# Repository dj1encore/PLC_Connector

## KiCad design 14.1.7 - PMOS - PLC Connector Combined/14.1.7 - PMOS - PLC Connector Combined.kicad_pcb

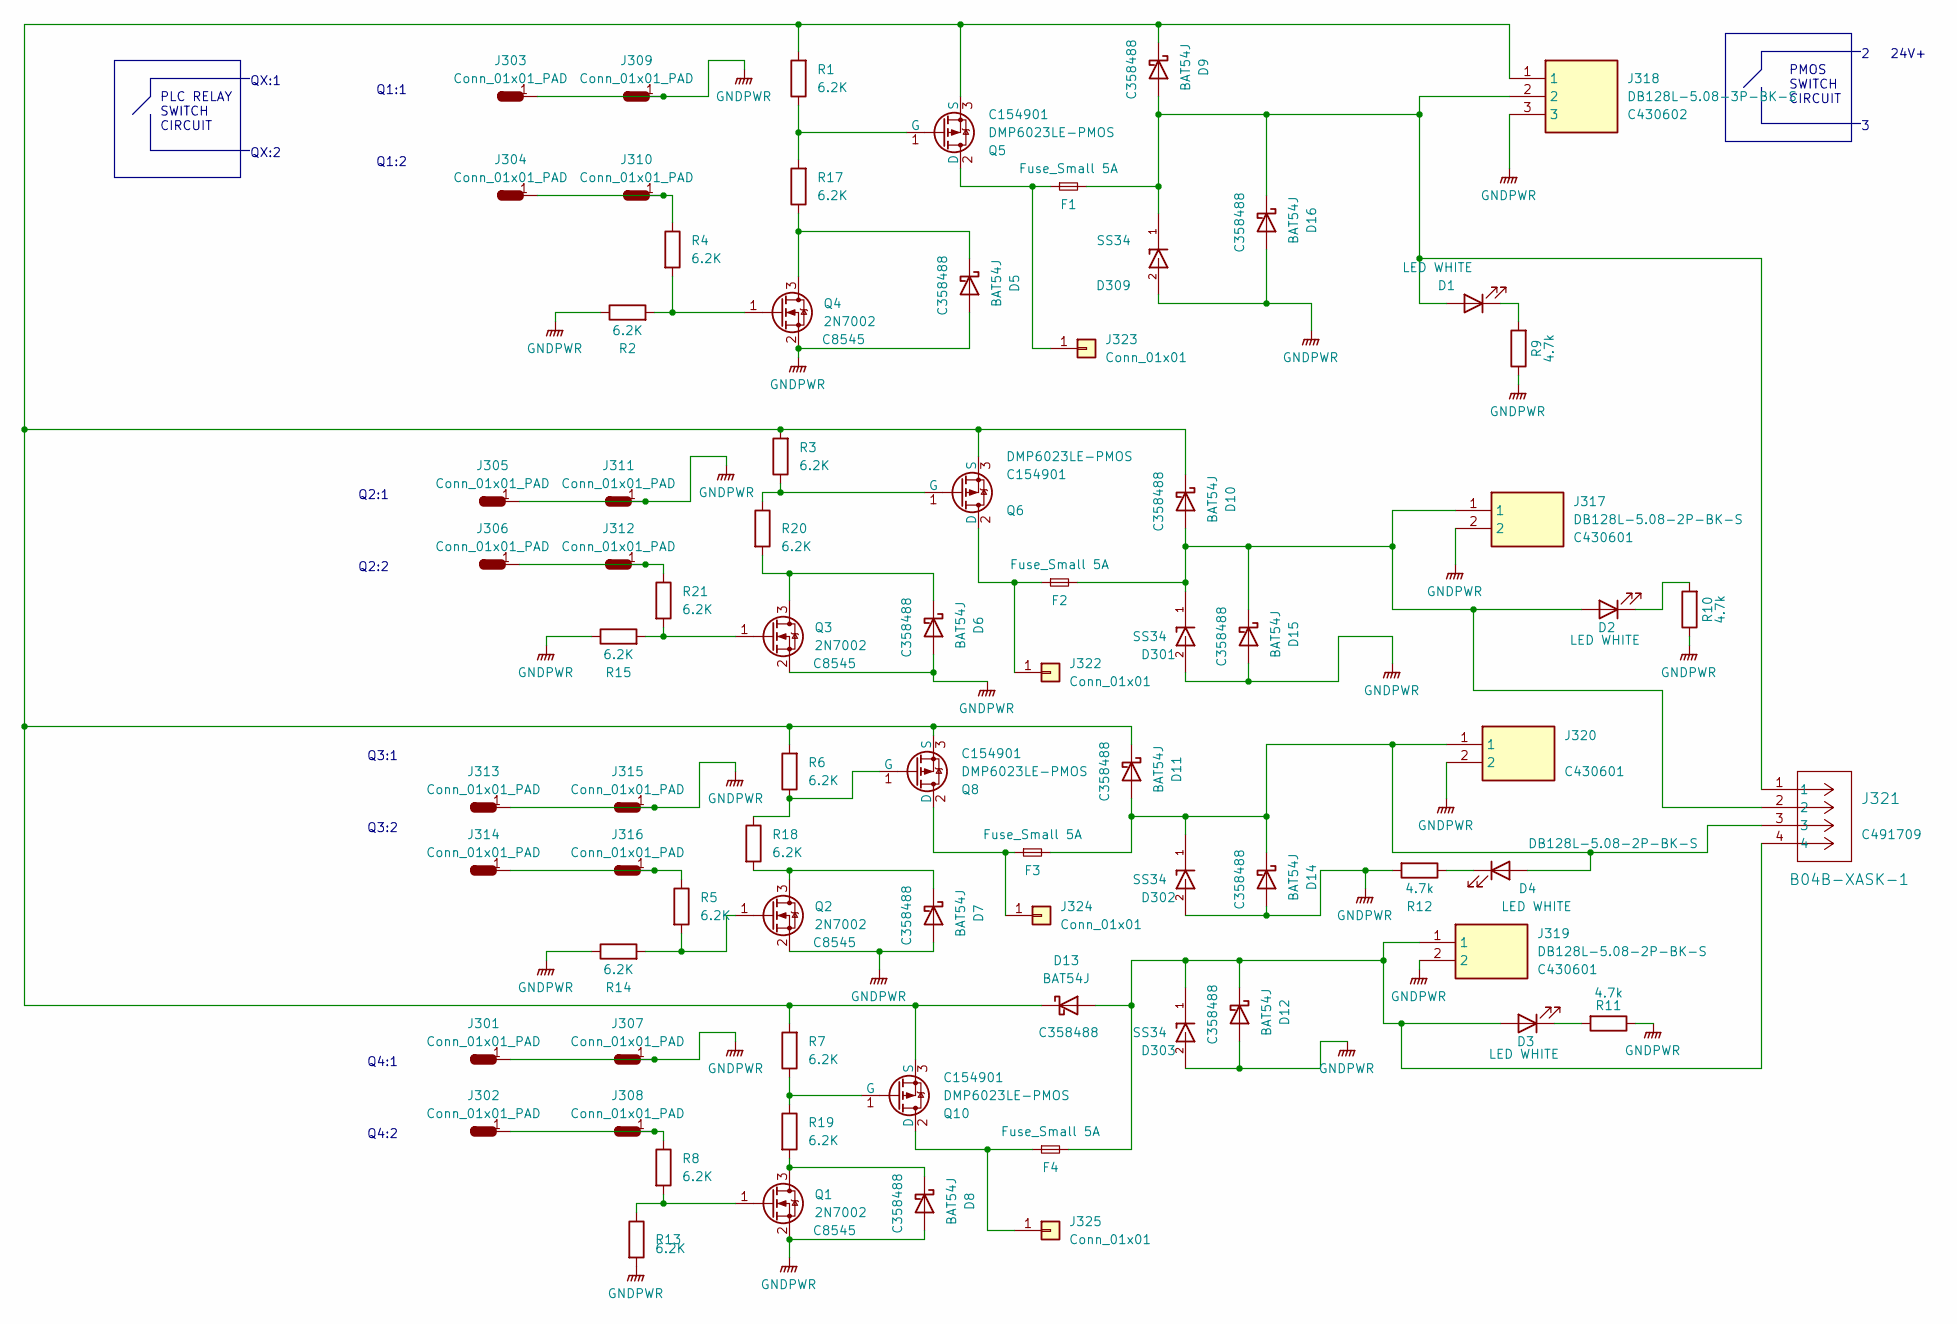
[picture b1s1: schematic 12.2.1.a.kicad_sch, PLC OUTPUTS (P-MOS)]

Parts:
D1, D2, D3, D4: LED WHITE; LED_0603_1608Metric; LCSC C2290
D5, D6, D7, D8, D9, D10, D11, D12, D13, D14, D15, D16: BAT54J; D_SOD-323F; LCSC C358488
D301, D302, D303, D309: SS34; D_SMA; LCSC C8678
F1, F2, F3, F4: Fuse_Small 5A; Fuse_1206_3216Metric_Pad1.42x1.75mm_HandSolder; LCSC C57525
J301, J302, J303, J304, J305, J306, J307, J308, J309, J310, J311, J312, J313, J314, J315, J316: Conn_01x01_PAD; Conn_pin_PLC
J317, J319, J320: DB128L-5.08-2P-BK-S; 1729128; Mouser Part Number 651-1729128
J318: DB128L-5.08-3P-BK-S; XY128V-A-5.08-3P; LCSC C430602
J321: B04B-XASK-1; CONN_B04B-XASK-1-A_JST; LCSC C491709
J322, J323, J324, J325: Conn_01x01; Pin_D0.7mm_L6.5mm_W1.8mm_FlatFork-MOD
Q1, Q2, Q3, Q4: 2N7002; SOT-23; LCSC C8545
Q5, Q6, Q8, Q10: DMP6023LE-PMOS; SOT-223 DMP6023LE; LCSC C154901
R1, R2, R3, R4, R5, R6, R7, R8, R13, R14, R15, R17, R18, R19, R20, R21: 6.2K; R_0603_1608Metric; LCSC C4260
R9, R10, R11, R12: 4.7k; R_0603_1608Metric; LCSC C88615

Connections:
GNDPWR: D5.2 (A), D6.2 (A), D7.2 (A), D8.2 (A), D12.2 (A), D14.2 (A), D15.2 (A), D16.2 (A), D301.2, D302.2, D303.2, D309.2, J301.1, J303.1, J305.1, J307.1, J309.1, J311.1, J313.1, J315.1, J317.2, J318.3, J319.2, J320.2, Q1.2 (S), Q2.2 (S), Q3.2 (S), Q4.2 (S), R2.1, R9.1, R10.1, R11.1, R12.2, R13.2, R14.1, R15.1
unnamed: D1.2 (A), D9.2 (A), D16.1 (K), D309.1, F1.2, J318.2, J321.1
unnamed: D1.1 (K), R9.2
unnamed: D2.1 (K), R10.2
unnamed: D3.1 (K), R11.2
unnamed: D4.1 (K), R12.1
unnamed: D5.1 (K), Q4.3 (D), R17.1
unnamed: D6.1 (K), Q3.3 (D), R20.2
unnamed: D7.1 (K), Q2.3 (D), R18.2
unnamed: D8.1 (K), Q1.3 (D), R19.2
unnamed: D2.2 (A), D10.2 (A), D15.1 (K), D301.1, F2.2, J317.1, J321.2
unnamed: D9.1 (K), D10.1 (K), D11.1 (K), D13.1 (K), J318.1, Q5.3 (S), Q6.3 (S), Q8.3 (S), Q10.3 (S), R1.2, R3.2, R6.2, R7.2
unnamed: D4.2 (A), D11.2 (A), D14.1 (K), D302.1, F3.2, J320.1, J321.3
unnamed: D3.2 (A), D12.1 (K), D13.2 (A), D303.1, F4.2, J319.1, J321.4
unnamed: J302.1, J308.1, R8.1
unnamed: J304.1, J310.1, R4.1
unnamed: J306.1, J312.1, R21.1
unnamed: J314.1, J316.1, R5.1
unnamed: F2.1, J322.1, Q6.2 (D)
unnamed: F1.1, J323.1, Q5.2 (D)
unnamed: F3.1, J324.1, Q8.2 (D)
unnamed: F4.1, J325.1, Q10.2 (D)
unnamed: Q1.1 (G), R8.2, R13.1
unnamed: Q2.1 (G), R5.2, R14.2
unnamed: Q3.1 (G), R15.2, R21.2
unnamed: Q4.1 (G), R2.2, R4.2
unnamed: Q5.1 (G), R1.1, R17.2
unnamed: Q6.1 (G), R3.1, R20.1
unnamed: Q8.1 (G), R6.1, R18.1
unnamed: Q10.1 (G), R7.1, R19.1

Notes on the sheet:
Q4:1
Q4:2
Q3:1
2 24V+
PMOS SWITCH CIRCUIT
QX:2
PLC RELAY SWITCH CIRCUIT
Q2:1
Q1:2
Q2:2
Q3:2
QX:1
Q1:1

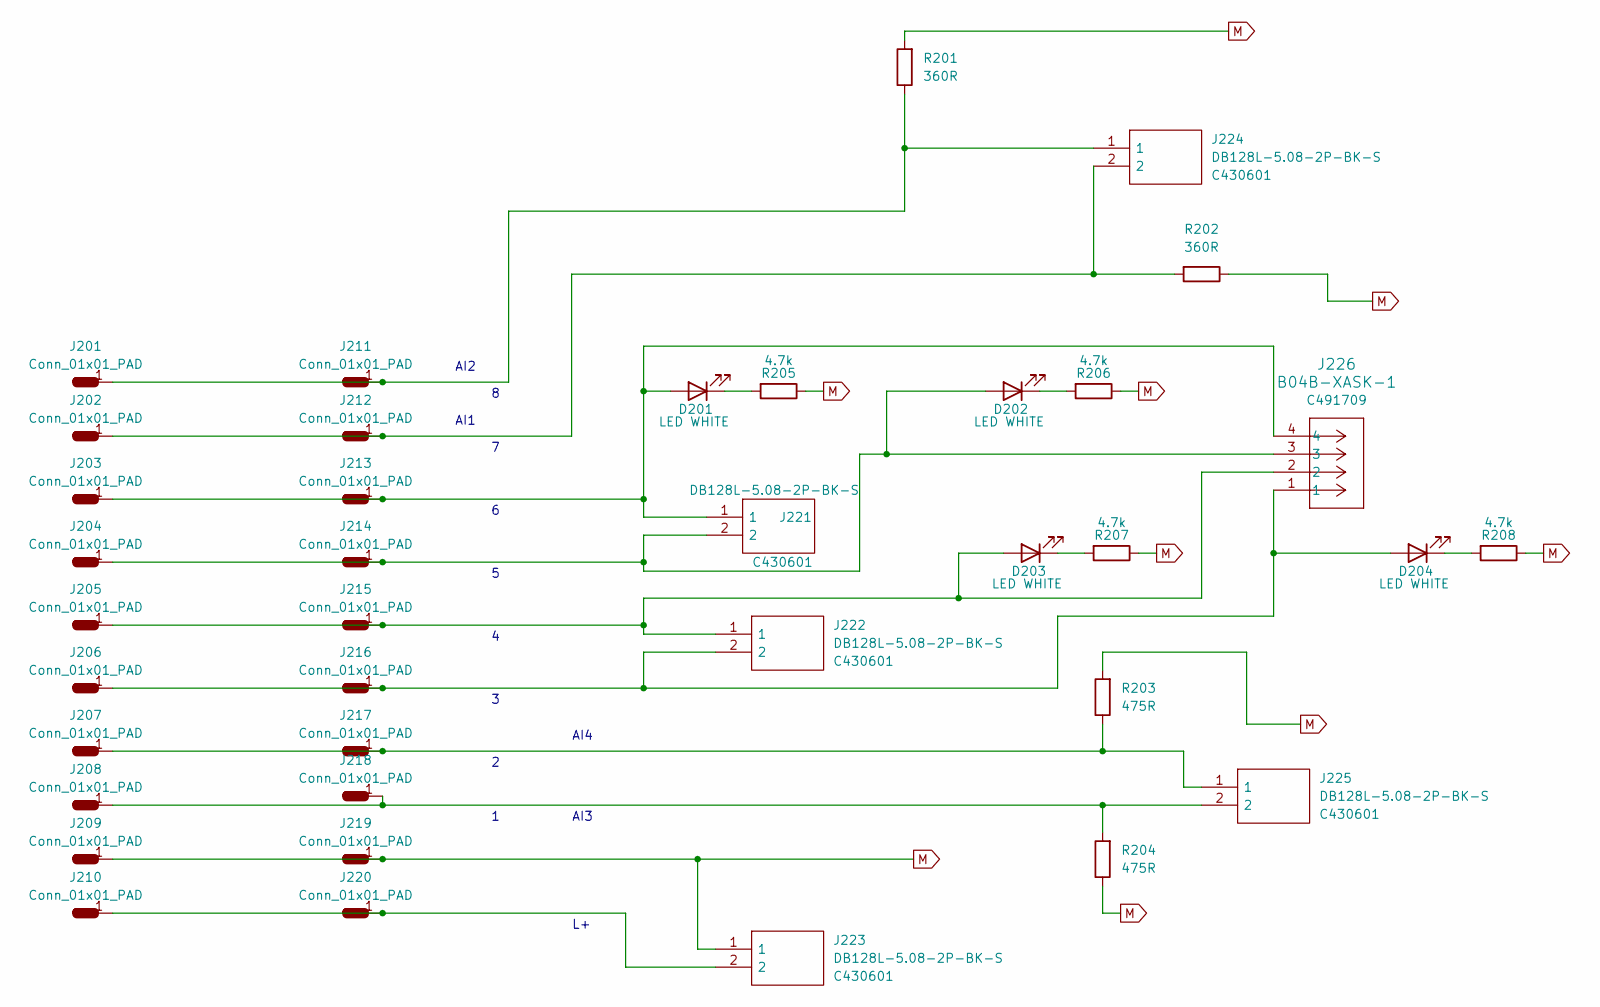
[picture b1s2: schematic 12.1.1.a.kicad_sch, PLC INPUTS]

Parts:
D201, D202, D203, D204: LED WHITE; LED_0603_1608Metric; LCSC C2290
J201, J202, J203, J204, J205, J206, J207, J208, J209, J210, J211, J212, J213, J214, J215, J216, J217, J218, J219, J220: Conn_01x01_PAD; Conn_pin_PLC
J221, J222, J223, J224, J225: DB128L-5.08-2P-BK-S; 1729128; Manufacturer_Part_Number 1729128; LCSC C430601
J226: B04B-XASK-1; CONN_B04B-XASK-1-A_JST; LCSC C491709
R201, R202: 360R; R_1206_3216Metric; LCSC C17932
R203, R204: 475R; R_1210_3225Metric; LCSC C784300
R205, R206, R207, R208: 4.7k; R_0603_1608Metric; LCSC C88615

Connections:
M: J209.1, J219.1, J223.1, R201.2, R202.1, R203.2, R204.1, R205.1, R206.1, R207.1, R208.1
unnamed: D201.2 (A), J203.1, J213.1, J221.1, J226.4
unnamed: D201.1 (K), R205.2
unnamed: D202.2 (A), J204.1, J214.1, J221.2, J226.3
unnamed: D202.1 (K), R206.2
unnamed: D203.2 (A), J205.1, J215.1, J222.1, J226.2
unnamed: D203.1 (K), R207.2
unnamed: D204.2 (A), J206.1, J216.1, J222.2, J226.1
unnamed: D204.1 (K), R208.2
unnamed: J201.1, J211.1, J224.1, R201.1
unnamed: J202.1, J212.1, J224.2, R202.2
unnamed: J207.1, J217.1, J225.1, R203.1
unnamed: J208.1, J218.1, J225.2, R204.2
unnamed: J210.1, J220.1, J223.2

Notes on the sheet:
AI2
AI3
AI4
AI1

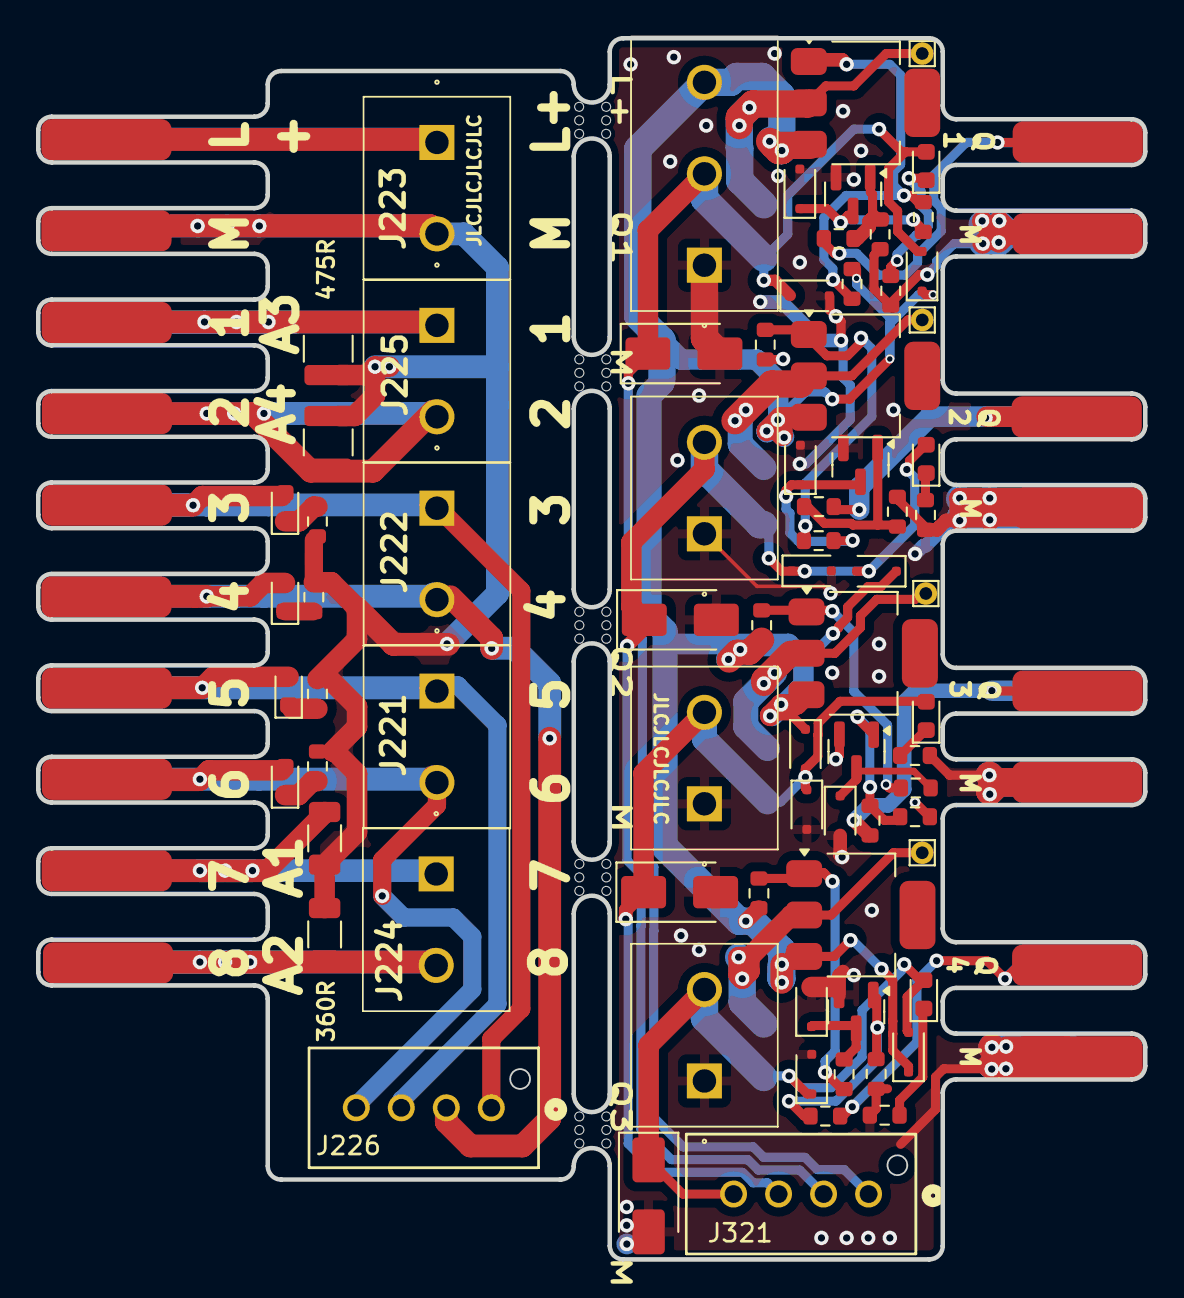
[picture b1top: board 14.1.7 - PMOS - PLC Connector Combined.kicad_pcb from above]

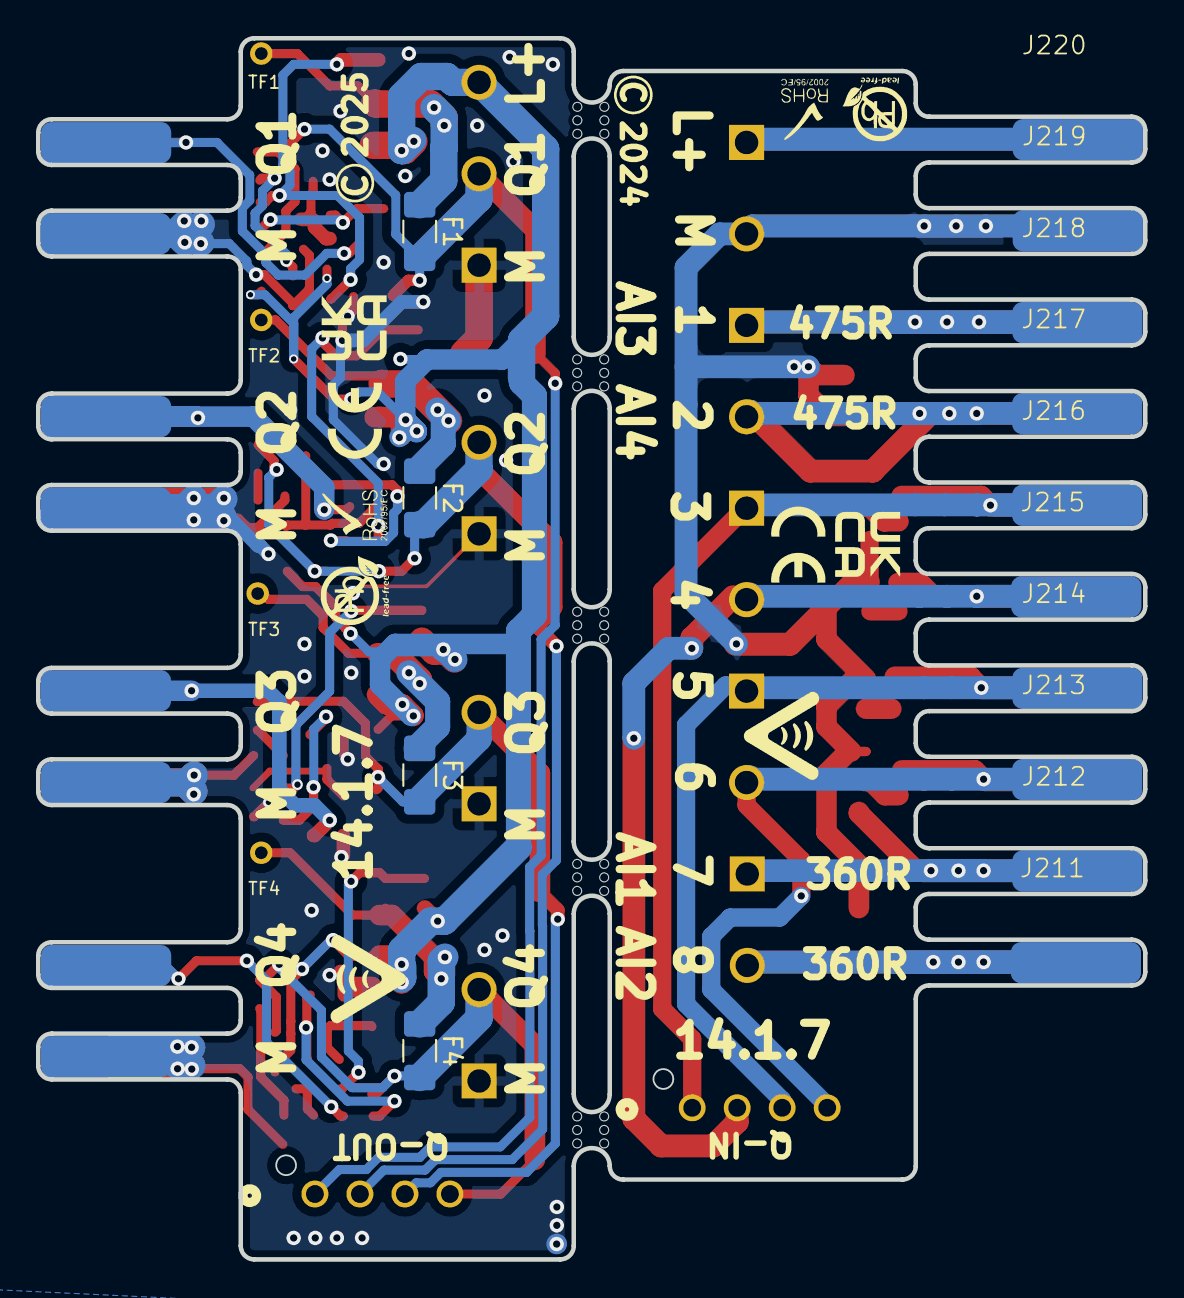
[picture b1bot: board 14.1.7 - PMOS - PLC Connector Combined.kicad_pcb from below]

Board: 2 copper layers, 61.5 x 67.8 mm, 120 parts (22 on the bottom side), 44 nets.

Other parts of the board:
mouse-bite-2mm-slot, mouse-bite-2mm-slot#2, mouse-bite-2mm-slot#3, mouse-bite-2mm-slot#4, mouse-bite-2mm-slot#5: VAL**; mouse-bite-2mm-slot

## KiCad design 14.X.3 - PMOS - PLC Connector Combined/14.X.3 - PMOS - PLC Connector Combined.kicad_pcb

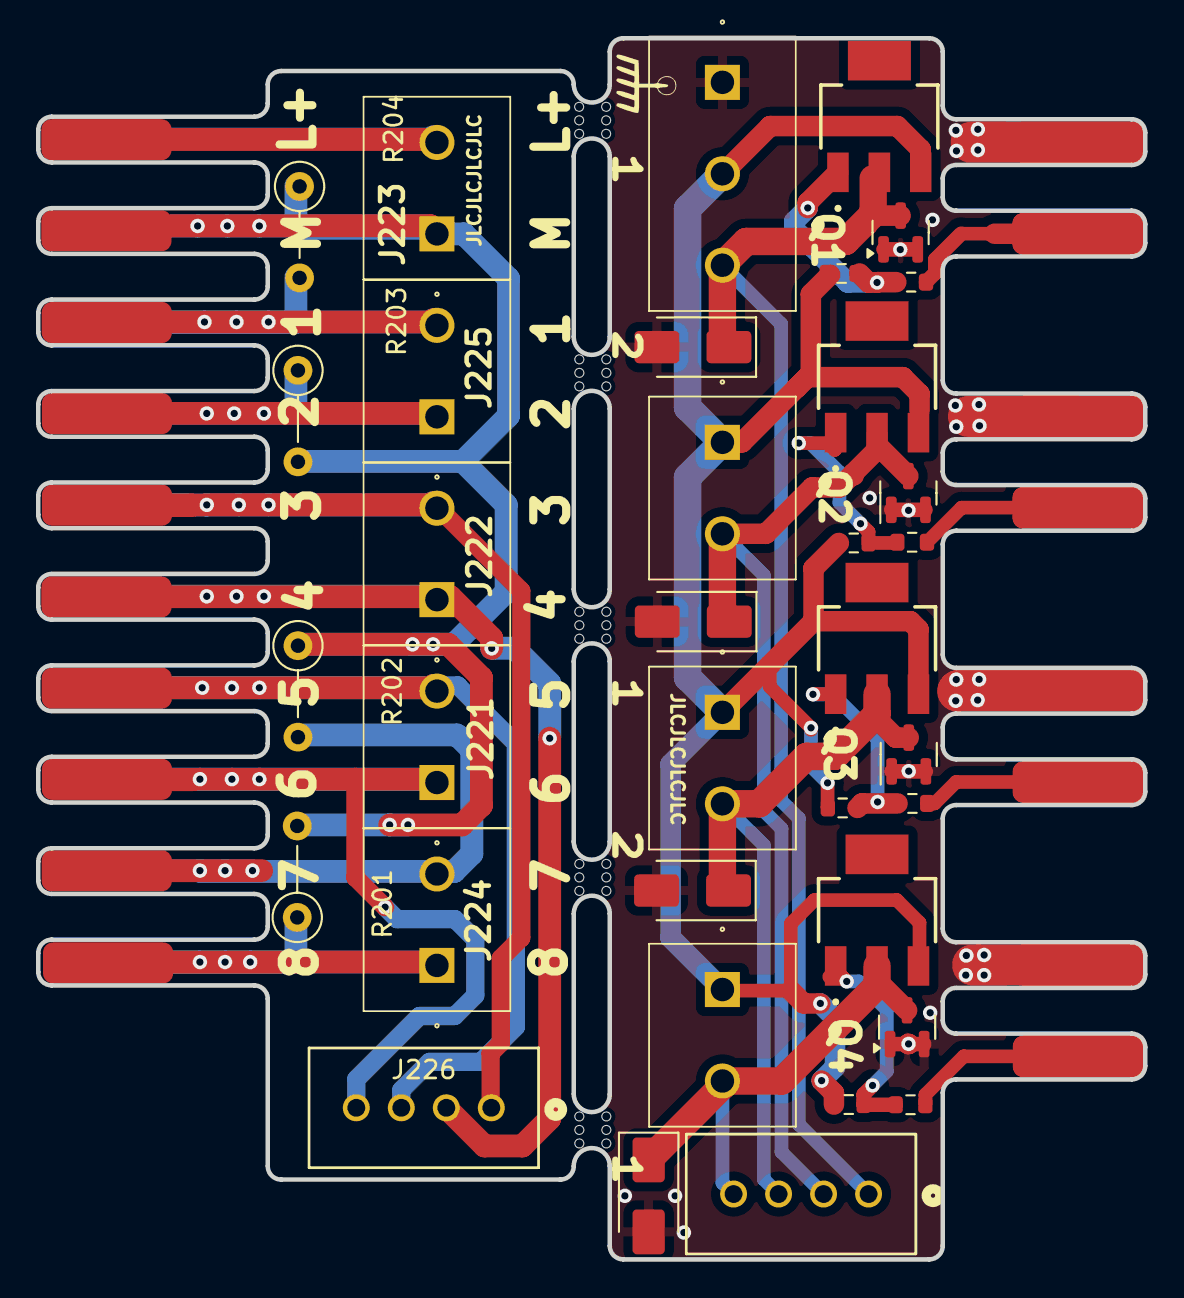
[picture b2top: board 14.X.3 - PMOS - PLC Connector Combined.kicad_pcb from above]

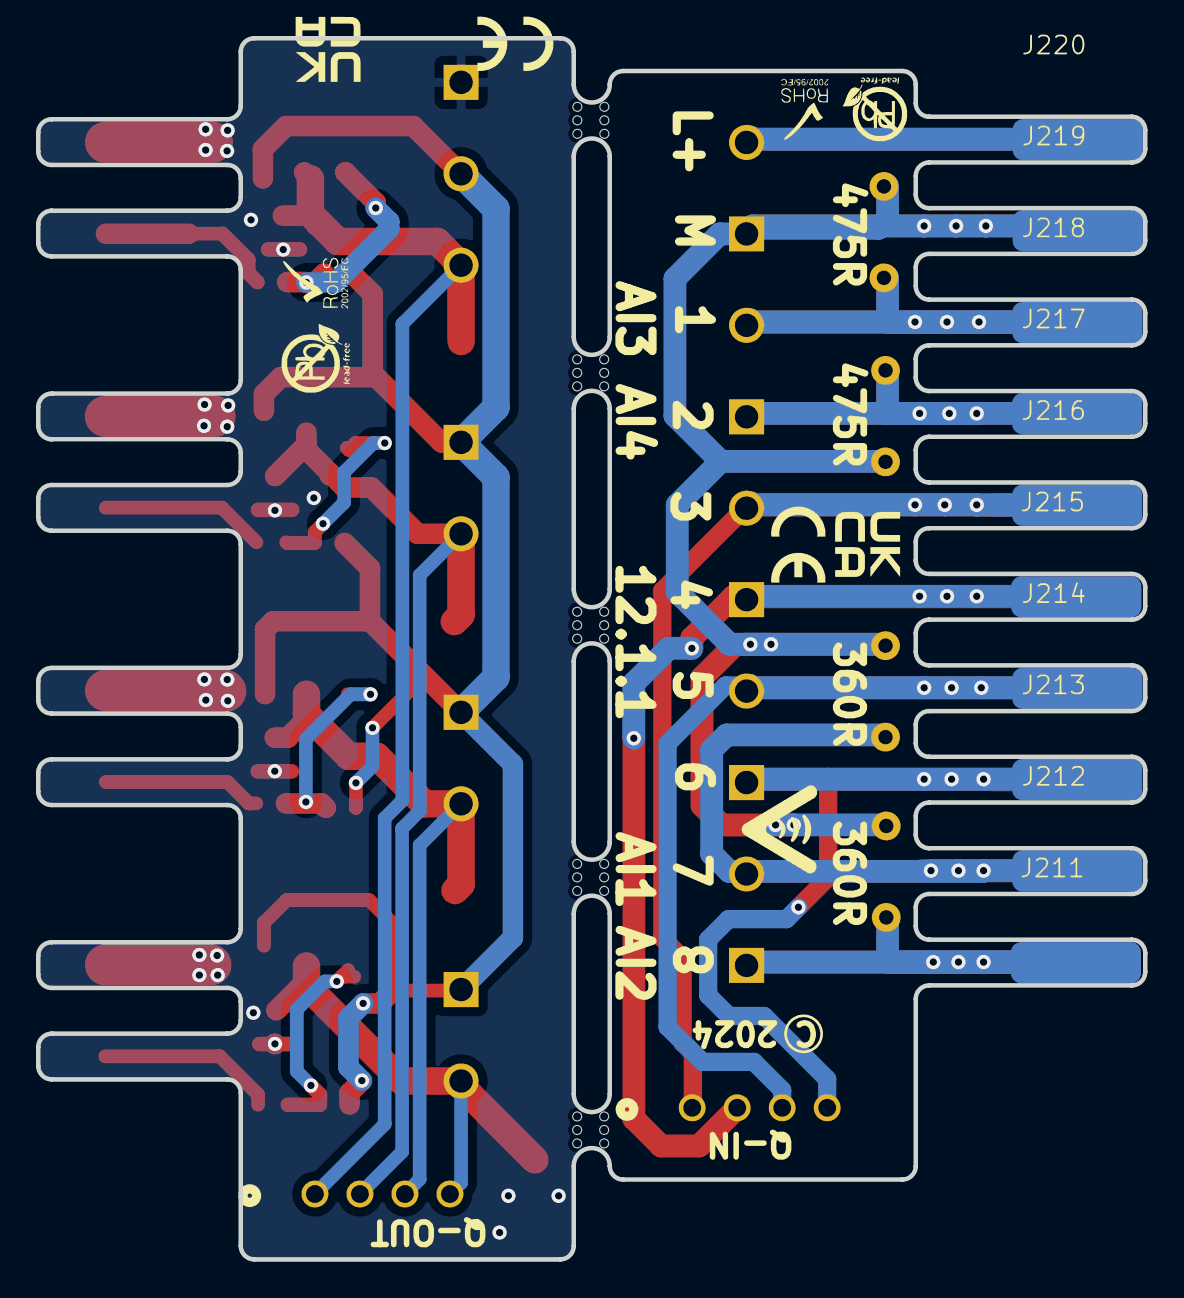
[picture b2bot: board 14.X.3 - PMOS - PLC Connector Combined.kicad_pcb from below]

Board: 2 copper layers, 61.5 x 67.8 mm, 76 parts (10 on the bottom side), 24 nets.

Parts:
D301, D302, D303, D309: SS34; D_SMA
D305, D306, D307, D308: BAT54C; SOT-23
J201, J202, J203, J204, J205, J206, J207, J208, J209, J210, J211, J212, J213, J214, J215, J216, J217, J218, J219, J220, J301, J302, J303, J304, J305, J306, J307, J308, J309, J310, J311, J312, J313, J314, J315, J316: Conn_01x01_PAD; Conn_pin_PLC
J221, J222, J223, J224, J225: Dorabo-DB128L_5_08_2P_BKS; 1729128
J226, J321: B04B-XASK-1; CONN_B04B-XASK-1_JST
J317, J319, J320: DB128L-5.08-2P-BK-S; 1729128
J318: DB128L-5.08-3P-BK-S; XY128V-A-5.08-3P
R1, R2, R3, R4, R5, R6, R7, R8: 6.2K; R_0603_1608Metric
R201, R202: 360R; R_Axial_DIN0207_L6.3mm_D2.5mm_P5.08mm_Vertical
R203, R204: 475R; R_Axial_DIN0207_L6.3mm_D2.5mm_P5.08mm_Vertical
U1, U2, U3, U4: DMP6023LE-13; SOT230P700X185-4N
mouse-bite-2mm-slot, mouse-bite-2mm-slot#2, mouse-bite-2mm-slot#3, mouse-bite-2mm-slot#4, mouse-bite-2mm-slot#5: VAL**; mouse-bite-2mm-slot

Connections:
GNDPWR: D301.2, D302.2, D303.2, D305.1, D305.2, D306.1, D306.2, D307.1, D307.2, D308.1, D308.2, D309.2, J301.1, J303.1, J305.1, J307.1, J309.1, J311.1, J313.1, J315.1, J318.1
M: J209.1, J219.1, J223.1, R201.2, R202.1, R203.2, R204.1
unnamed: D301.1, D308.3, J317.2, J321.2, U2.2
unnamed: D302.1, D306.3, J320.2, J321.3, U3.2
unnamed: D303.1, D305.3, J319.2, J321.4, U4.2
unnamed: D307.3, D309.1, J318.3, J321.1, U1.2
unnamed: J201.1, J211.1, J224.1, R201.1
unnamed: J202.1, J212.1, J224.2, R202.2
unnamed: J203.1, J213.1, J221.1, J226.4
unnamed: J204.1, J214.1, J221.2, J226.3
unnamed: J205.1, J215.1, J222.1, J226.2
unnamed: J206.1, J216.1, J222.2, J226.1
unnamed: J207.1, J217.1, J225.1, R203.1
unnamed: J208.1, J218.1, J225.2, R204.2
unnamed: J210.1, J220.1, J223.2
unnamed: J302.1, J308.1, R8.2
unnamed: J304.1, J310.1, R2.2
unnamed: J306.1, J312.1, R4.2
unnamed: J314.1, J316.1, R5.2
unnamed: J317.1, J318.2, J319.1, J320.1, R1.2, R3.2, R6.2, R7.2, U1.3, U2.3, U3.3, U4.3
unnamed: R1.1, R2.1, U1.1
unnamed: R3.1, R4.1, U2.1
unnamed: R5.1, R6.1, U3.1
unnamed: R7.1, R8.1, U4.1

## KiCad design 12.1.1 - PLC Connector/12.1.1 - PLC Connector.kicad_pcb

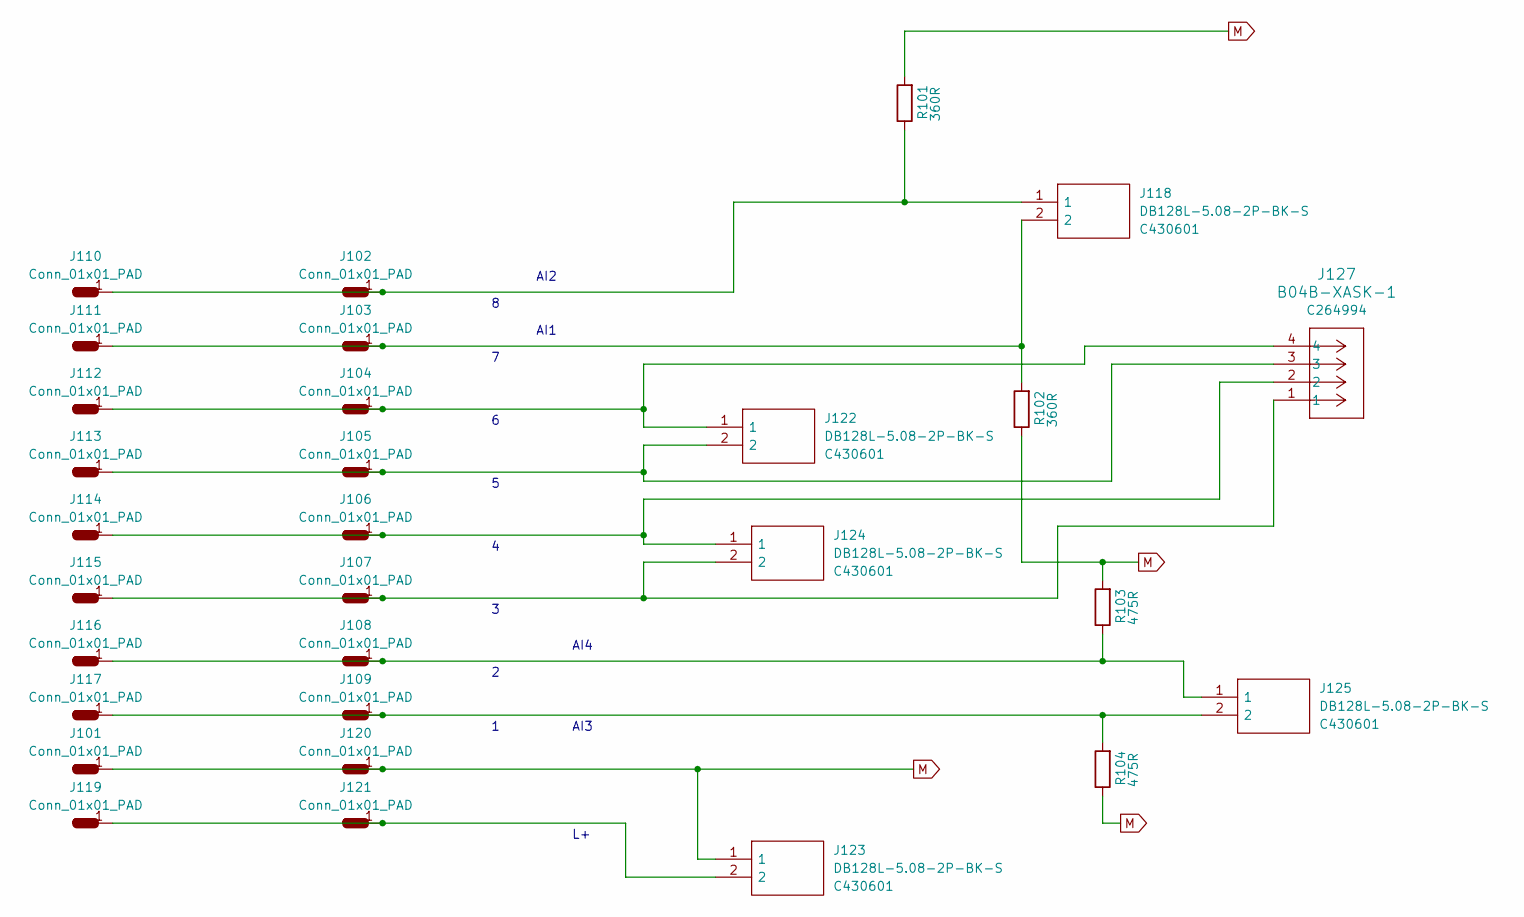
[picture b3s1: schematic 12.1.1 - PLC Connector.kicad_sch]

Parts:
J101, J102, J103, J104, J105, J106, J107, J108, J109, J110, J111, J112, J113, J114, J115, J116, J117, J119, J120, J121: Conn_01x01_PAD; Conn_pin_PLC
J118, J122, J123, J124, J125: DB128L-5.08-2P-BK-S; 1729128; Manufacturer_Part_Number 1729128; LCSC C430601
J127: B04B-XASK-1; CONN_B04B-XASK-1_JST; LCSC C264994
R101, R102: 360R; R_Axial_DIN0207_L6.3mm_D2.5mm_P5.08mm_Vertical; LCSC C58649
R103, R104: 475R; R_Axial_DIN0207_L6.3mm_D2.5mm_P5.08mm_Vertical; LCSC C138206

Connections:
M: J101.1, J120.1, J123.1, R101.2, R102.1, R103.2, R104.1
unnamed: J102.1, J110.1, J118.1, R101.1
unnamed: J103.1, J111.1, J118.2, R102.2
unnamed 3: J104.1, J112.1, J122.1, J127.4; also elsewhere on the board
unnamed 4: J105.1, J113.1, J122.2, J127.3; also elsewhere on the board
unnamed 5: J106.1, J114.1, J124.1, J127.2; also elsewhere on the board
unnamed 6: J107.1, J115.1, J124.2, J127.1; also elsewhere on the board
unnamed: J108.1, J116.1, J125.1, R103.1
unnamed: J109.1, J117.1, J125.2, R104.2
unnamed: J119.1, J121.1, J123.2

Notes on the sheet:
AI2
AI4
AI3
AI1

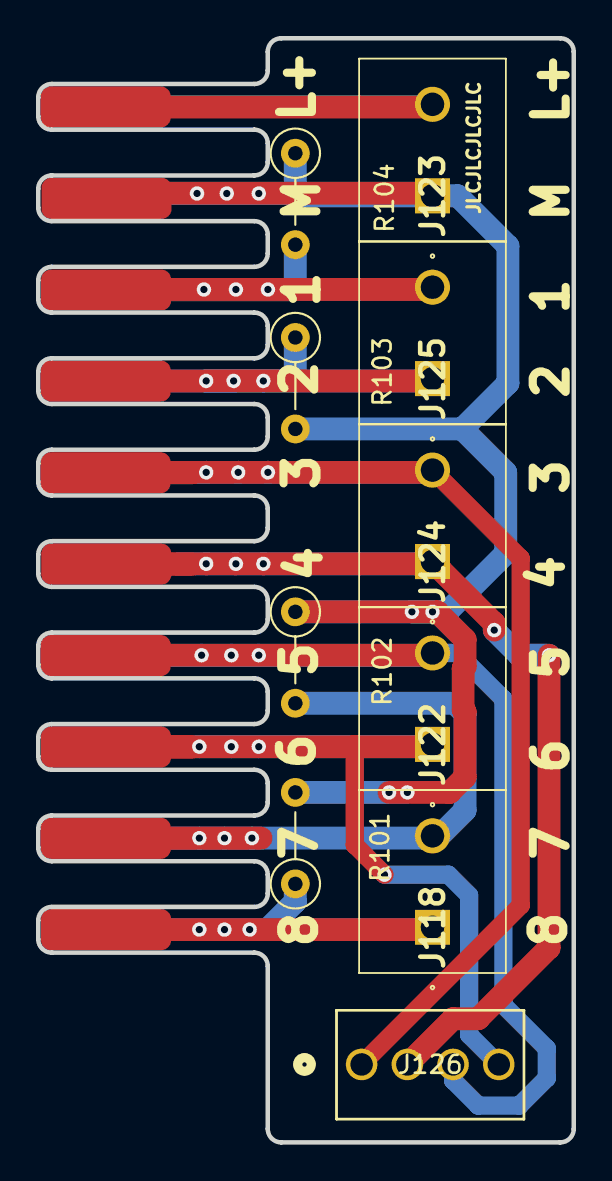
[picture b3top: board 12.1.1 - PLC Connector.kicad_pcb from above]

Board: 2 copper layers, 29.8 x 61.3 mm, 30 parts (1 on the bottom side), 10 nets.

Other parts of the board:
J126: 22292041; CONN_22-29-2041_MOL

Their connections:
unnamed 3: J126.4; also elsewhere on the board
unnamed 4: J126.3; also elsewhere on the board
unnamed 5: J126.2; also elsewhere on the board
unnamed 6: J126.1; also elsewhere on the board

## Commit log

2024-07-21 Initial
2024-07-21 12.2.1 front silk
2024-07-21 combined template
2024-07-22 worked on layout, added V-Cut lines
2024-07-23 change pcb edge cuts
2024-07-25 As built
2024-08-04 Version 12.x.2
2024-08-04 As purchaced 12.X.2
2024-08-15 as purchaced
2024-08-15 updatd board outline
2024-11-05 Version 14.x.4 PMOS Design
2024-11-07 orientation of U1,U2,U3 and U4
2024-11-09 PCB Layout 14.1.4
2024-11-09 PCB Layout 14.1.4 with Gerber
2024-11-09 fixed non connected tracks
2024-11-16 20241124
2024-11-18 gerber
2024-11-29 14.1.15 with PMOS fixed
2025-09-10 4.1.6
2025-09-10 track thickness
2025-09-13 14.1.7 with probe point for testing fuse
2025-09-14 updated 14.1.7
